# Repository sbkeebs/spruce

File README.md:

# Spruce

not the tree (actually, a split [Bruce](https://www.jlw-kb.com/products/bruce-the-keyboard-the-pcb)).

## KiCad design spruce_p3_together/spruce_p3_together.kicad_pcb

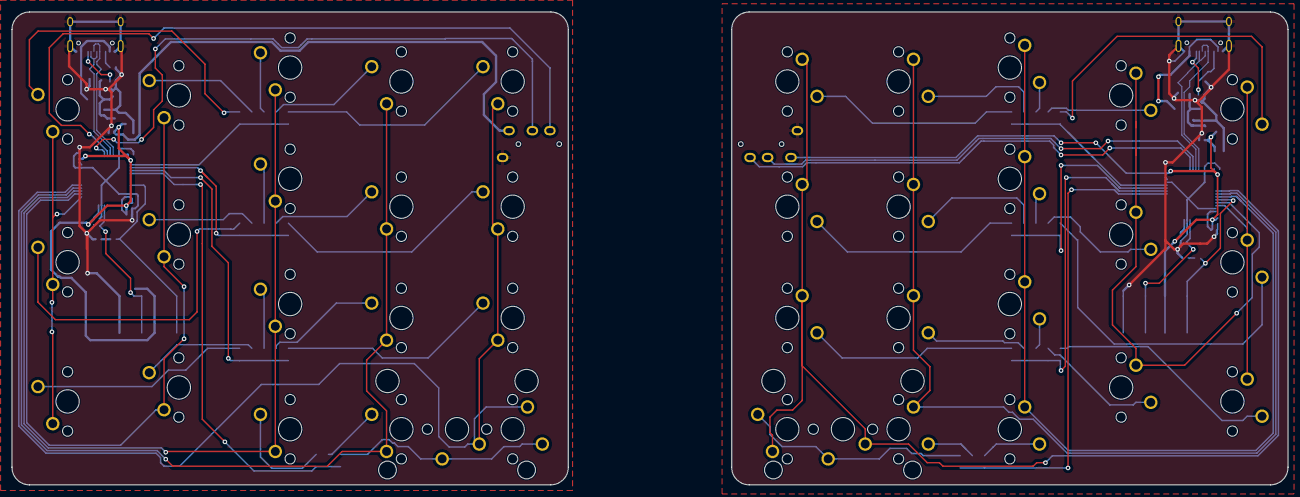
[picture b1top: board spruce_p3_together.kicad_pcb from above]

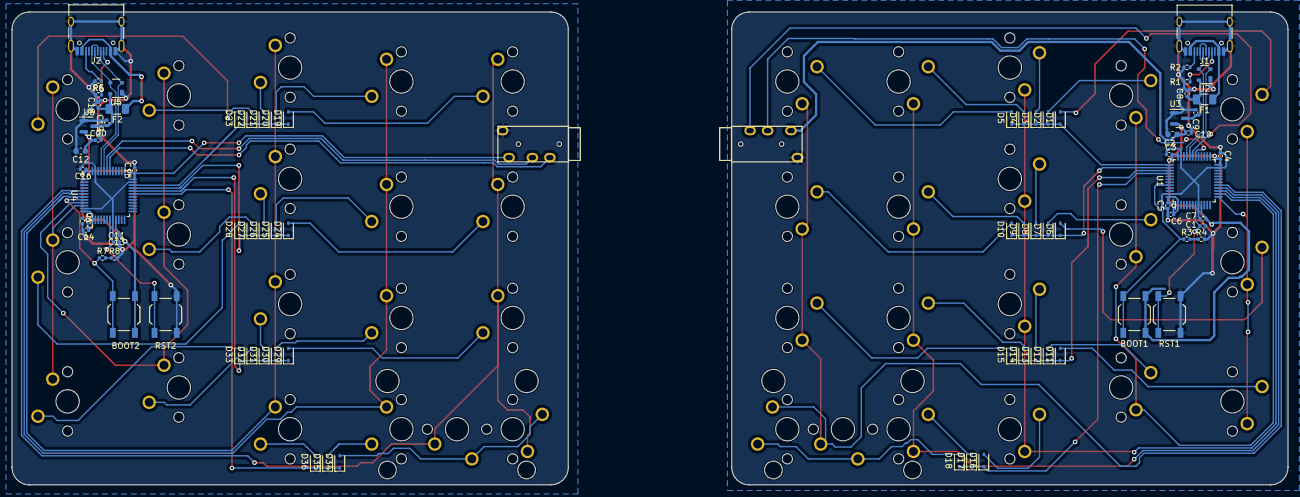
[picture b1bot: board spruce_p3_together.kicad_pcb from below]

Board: 2 copper layers, 218.5 x 81.0 mm, 120 parts (80 on the bottom side), 80 nets.

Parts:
BOOT1, BOOT2: SW_SPST; SW_SPST_TL3342
C1, C3, C4, C5, C6, C7, C8, C11, C13, C14, C15, C16, C17, C18: 100nF; C_0402_1005Metric
C2, C12: 10uF; C_0603_1608Metric
C9, C10, C19, C20: 1uF; C_0402_1005Metric
D1, D2, D3, D4, D5, D6, D7, D8, D9, D10, D11, D12, D13, D14, D15, D16, D17, D18, D19, D20, D21, D22, D23, D24, D25, D26, D27, D28, D29, D30, D31, D32, D33, D34, D35, D36: D_Small; D_SOD-323
F1, F2: 500mA; Fuse_1206_3216Metric
J1, J2: USB_C_Receptacle_USB2.0; USB_C_Receptacle_HRO_TYPE-C-31-M-12
L_MX1, L_MX12: MX_SW_solder; SW_MX_1.75u
L_MX2, L_MX11: MX_SW_solder; SW_MX_1.5u
L_MX3, L_MX6, L_MX7, L_MX8, L_MX9, L_MX10, L_MX14, L_MX15, L_MX16, L_MX17, L_MX18, L_MX19: MX_SW_solder; SW_MX_1u
L_MX4, L_MX5, L_MX13: MX_SW_solder; SW_MX_1.25u
R1, R2, R3, R4, R5, R6, R7, R8: 5.1k; R_0402_1005Metric
RST1, RST2: SW_SPST; SW_SPST_TL3342
R_MX1, R_MX2, R_MX13: MX_SW_solder; SW_MX_1.25u
R_MX3, R_MX6, R_MX7, R_MX8, R_MX9, R_MX10, R_MX11, R_MX12, R_MX16, R_MX17, R_MX18, R_MX19: MX_SW_solder; SW_MX_1u
R_MX4, R_MX15: MX_SW_solder; SW_MX_1.5u
R_MX5, R_MX14: MX_SW_solder; SW_MX_1.75u
S1, S2: MX_stab; STAB_MX_2u
U1, U4: STM32F072CBT6; LQFP-48_7x7mm_P0.5mm
U2, U5: PRTR5V0U2X; SOT-143
U3, U6: XC6206PxxxMR-Regulator_Linear; SOT-23
U7, U8: TRRS; TRRS-PJ-320A

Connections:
+3.3VA: BOOT2.1 (A), C12.1, C13.1, C14.1, C15.1, C16.1, C17.1, C20.1, U4.1 (VBAT), U4.9 (VDDA), U4.24 (VDD), U4.36 (VDDIO2), U4.48 (VDD), U6.2 (VO), U8.2 (TIP)
+3V3: BOOT1.1 (A), C2.1, C3.1, C4.1, C5.1, C6.1, C7.1, C10.1, U1.1 (VBAT), U1.9 (VDDA), U1.24 (VDD), U1.36 (VDDIO2), U1.48 (VDD), U3.2 (VO), U7.2 (TIP)
+5V: C8.1, C9.1, F1.2, U2.4 (VCC), U3.3 (VI)
+5VA: C18.1, C19.1, F2.2, U5.4 (VCC), U6.3 (VI)
GND: C1.2, C2.2, C3.2, C4.2, C5.2, C6.2, C7.2, C8.2, C9.2, C10.2, J1.A1 (GND), J1.A12 (GND), J1.B1 (GND), J1.B12 (GND), J1.S1 (SHIELD), R1.1, R2.2, R4.2, RST1.2 (B), U1.8 (VSSA), U1.23 (VSS), U1.35 (VSS), U1.47 (VSS), U2.1 (GND), U3.1 (GND), U7.1 (SLEEVE)
GND1: C11.2, C12.2, C13.2, C14.2, C15.2, C16.2, C17.2, C18.2, C19.2, C20.2, J2.A1 (GND), J2.A12 (GND), J2.B1 (GND), J2.B12 (GND), J2.S1 (SHIELD), R5.1, R6.2, R8.2, RST2.2 (B), U4.8 (VSSA), U4.23 (VSS), U4.35 (VSS), U4.47 (VSS), U5.1 (GND), U6.1 (GND), U8.1 (SLEEVE)
L_BOOT0: BOOT1.2 (B), R3.1, U1.44 (BOOT0)
L_C0: L_MX1.1, L_MX6.1, L_MX11.1, U1.13 (PA3)
L_C1: L_MX2.1, L_MX7.1, L_MX12.1, U1.14 (PA4)
L_C2: L_MX3.1, L_MX8.1, L_MX13.1, L_MX16.1, U1.15 (PA5)
L_C3: L_MX4.1, L_MX9.1, L_MX14.1, L_MX17.1, U1.16 (PA6)
L_C4: L_MX5.1, L_MX10.1, L_MX15.1, L_MX18.1, L_MX19.1, U1.17 (PA7)
L_D+: J1.A6 (D+), J1.B6 (D+), U1.33 (PA12), U2.3 (I/O2)
L_D-: J1.A7 (D-), J1.B7 (D-), U1.32 (PA11), U2.2 (I/O1)
L_NRST: C1.1, RST1.1 (A), U1.7 (NRST)
L_R0: D1.1 (K), D2.1 (K), D3.1 (K), D4.1 (K), D5.1 (K), U1.37 (PA14)
L_R1: D6.1 (K), D7.1 (K), D8.1 (K), D9.1 (K), D10.1 (K), U1.38 (PA15)
L_R2: D11.1 (K), D12.1 (K), D13.1 (K), D14.1 (K), D15.1 (K), U1.39 (PB3)
L_R3: D16.1 (K), D17.1 (K), D18.1 (K), U1.40 (PB4)
L_RX: U1.31 (PA10), U7.4 (RING2)
L_TX: U1.30 (PA9), U7.3 (RING1)
L_VBUS: F1.1, J1.A4 (VBUS), J1.A9 (VBUS), J1.B4 (VBUS), J1.B9 (VBUS)
unnamed: D1.2 (A), L_MX1.2
unnamed: D2.2 (A), L_MX2.2
unnamed: D3.2 (A), L_MX3.2
unnamed: D4.2 (A), L_MX4.2
unnamed: D5.2 (A), L_MX5.2
unnamed: D6.2 (A), L_MX6.2
unnamed: D7.2 (A), L_MX7.2
unnamed: D8.2 (A), L_MX8.2
unnamed: D9.2 (A), L_MX9.2
unnamed: D10.2 (A), L_MX10.2
unnamed: D11.2 (A), L_MX11.2
unnamed: D12.2 (A), L_MX12.2
unnamed: D13.2 (A), L_MX13.2
unnamed: D14.2 (A), L_MX14.2
unnamed: D15.2 (A), L_MX15.2
unnamed: D16.2 (A), L_MX16.2
unnamed: D17.2 (A), L_MX17.2
unnamed: D18.2 (A), L_MX18.2, L_MX19.2
unnamed: D19.2 (A), R_MX1.2
unnamed: D20.2 (A), R_MX2.2
unnamed: D21.2 (A), R_MX3.2
unnamed: D22.2 (A), R_MX4.2
unnamed: D23.2 (A), R_MX5.2
unnamed: D24.2 (A), R_MX6.2
unnamed: D25.2 (A), R_MX7.2
unnamed: D26.2 (A), R_MX8.2
unnamed: D27.2 (A), R_MX9.2
unnamed: D28.2 (A), R_MX10.2
unnamed: D29.2 (A), R_MX11.2
unnamed: D30.2 (A), R_MX12.2
unnamed: D31.2 (A), R_MX13.2
unnamed: D32.2 (A), R_MX14.2
unnamed: D33.2 (A), R_MX15.2
unnamed: D34.2 (A), R_MX16.2, R_MX17.2
unnamed: D35.2 (A), R_MX18.2
unnamed: D36.2 (A), R_MX19.2
unnamed: J1.A5 (CC1), R1.2
unnamed: J1.B5 (CC2), R2.1
unnamed: J2.A5 (CC1), R5.2
unnamed: J2.B5 (CC2), R6.1
unnamed: R3.2, R4.1
unnamed: R7.2, R8.1
R_BOOT0: BOOT2.2 (B), R7.1, U4.44 (BOOT0)
R_C0: R_MX1.1, R_MX6.1, R_MX11.1, R_MX16.1, R_MX17.1, U4.41 (PB5)
R_C1: R_MX2.1, R_MX7.1, R_MX12.1, R_MX18.1, U4.42 (PB6)
R_C2: R_MX3.1, R_MX8.1, R_MX13.1, R_MX19.1, U4.43 (PB7)
R_C3: R_MX4.1, R_MX9.1, R_MX14.1, U4.45 (PB8)
R_C4: R_MX5.1, R_MX10.1, R_MX15.1, U4.46 (PB9)
R_D+: J2.A6 (D+), J2.B6 (D+), U4.33 (PA12), U5.3 (I/O2)
R_D-: J2.A7 (D-), J2.B7 (D-), U4.32 (PA11), U5.2 (I/O1)
R_NRST: C11.1, RST2.1 (A), U4.7 (NRST)
R_R0: D19.1 (K), D20.1 (K), D21.1 (K), D22.1 (K), D23.1 (K), U4.22 (PB11)
R_R1: D24.1 (K), D25.1 (K), D26.1 (K), D27.1 (K), D28.1 (K), U4.21 (PB10)
R_R2: D29.1 (K), D30.1 (K), D31.1 (K), D32.1 (K), D33.1 (K), U4.20 (PB2)
R_R3: D34.1 (K), D35.1 (K), D36.1 (K), U4.19 (PB1)
R_RX: U4.31 (PA10), U8.3 (RING1)
R_TX: U4.30 (PA9), U8.4 (RING2)
R_VBUS: F2.1, J2.A4 (VBUS), J2.A9 (VBUS), J2.B4 (VBUS), J2.B9 (VBUS)

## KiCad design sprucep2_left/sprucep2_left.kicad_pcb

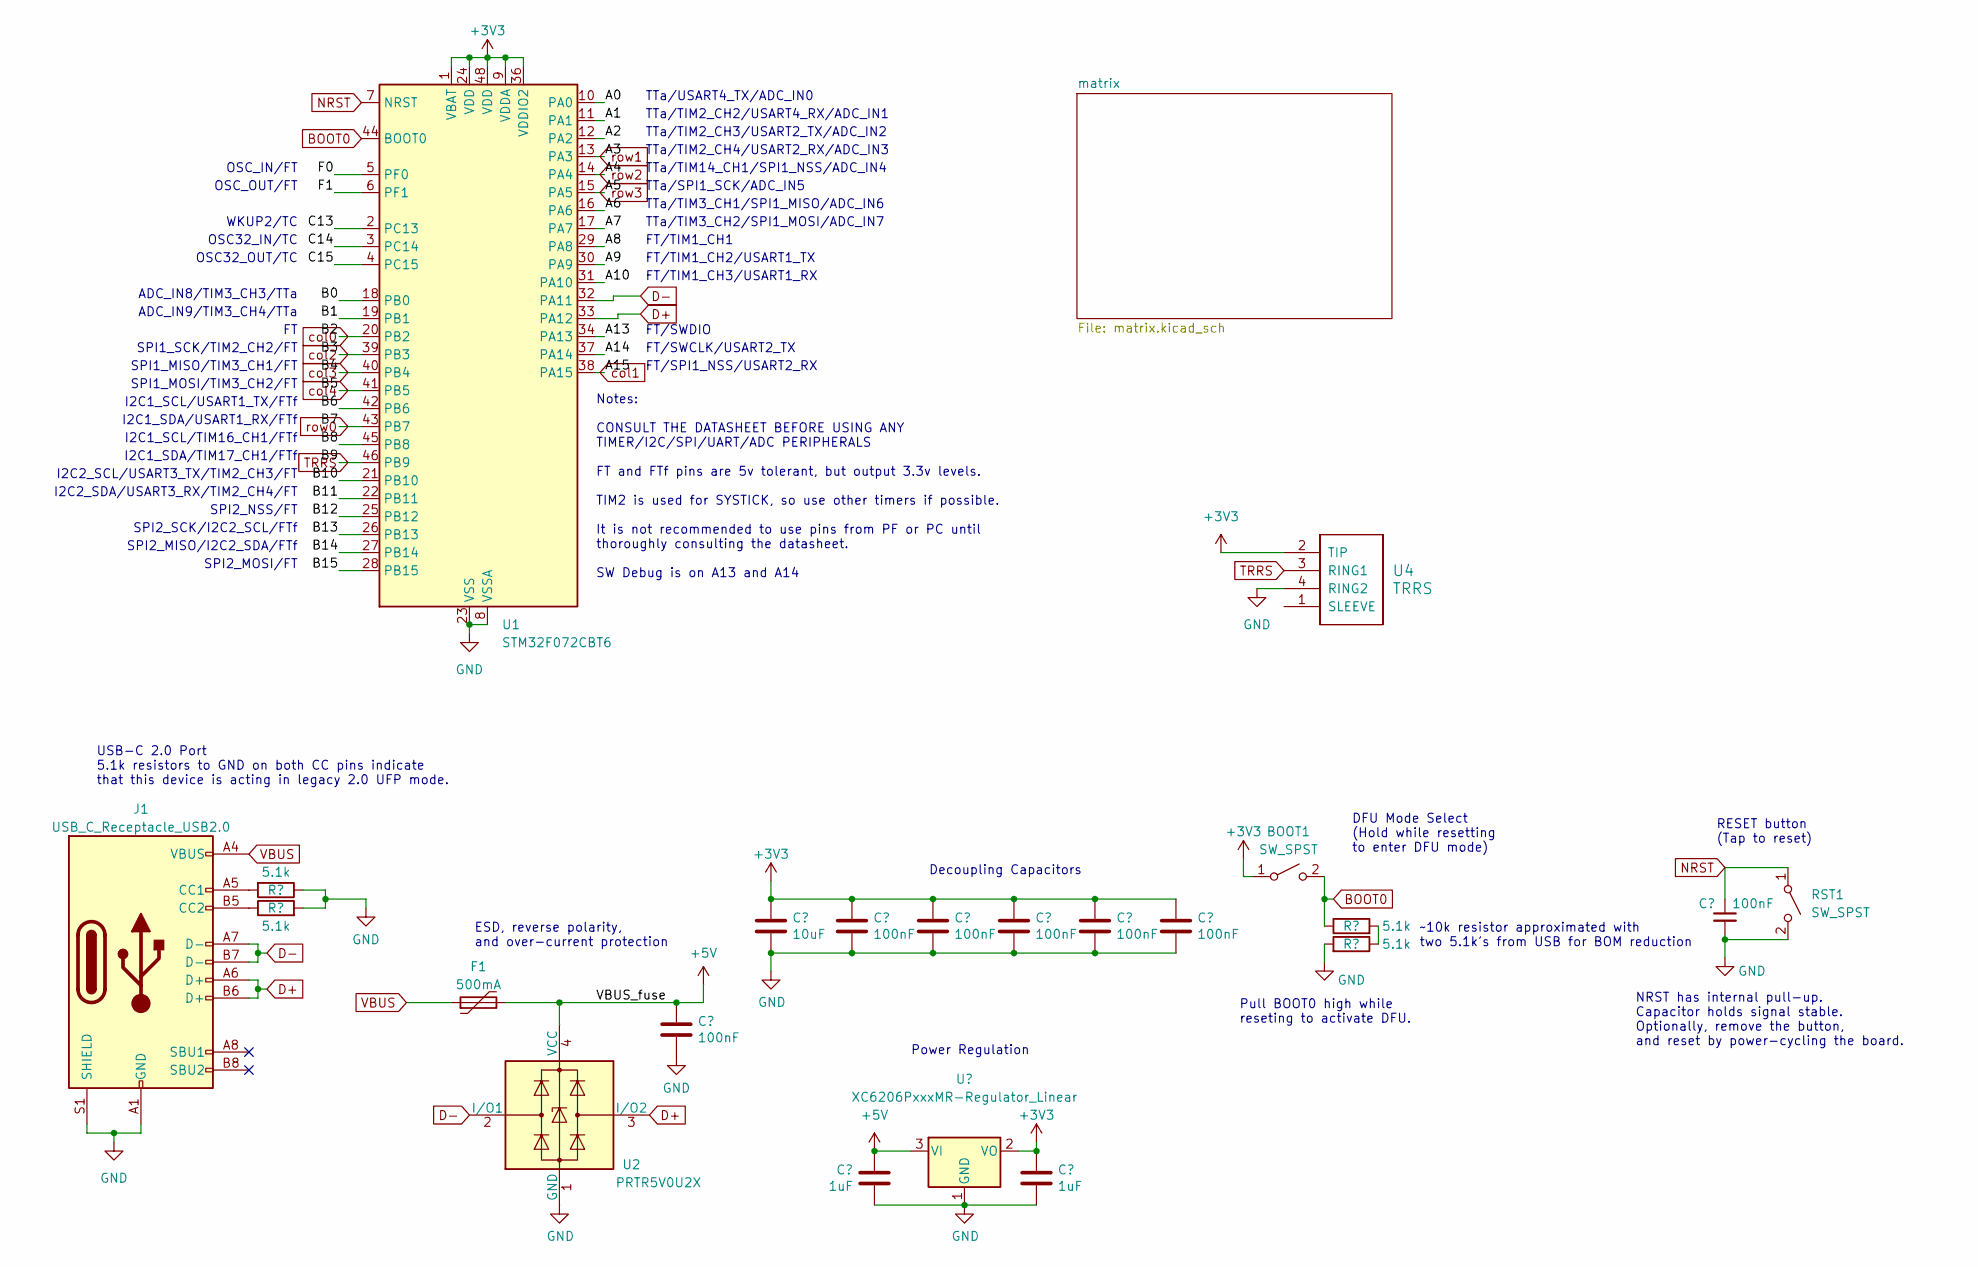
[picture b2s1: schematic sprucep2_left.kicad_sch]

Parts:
BOOT1: SW_SPST; SW_SPST_TL3342
C1, C3, C4, C5, C6, C7, C8: 100nF; C_0402_1005Metric; LCSC C307331
C2: 10uF; C_0603_1608Metric; LCSC C307331
C9, C10: 1uF; C_0402_1005Metric; LCSC C307331
F1: 500mA; Fuse_1206_3216Metric; LCSC C135341
J1: USB_C_Receptacle_USB2.0; USB_C_Receptacle_HRO_TYPE-C-31-M-12; JlcRotOffset 180
R1, R2, R3, R4: 5.1k; R_0402_1005Metric
RST1: SW_SPST; SW_SPST_TL3342
U1: STM32F072CBT6; LQFP-48_7x7mm_P0.5mm; JlcRotOffset 90
U2: PRTR5V0U2X; SOT-143; LCSC C2827688
U3: XC6206PxxxMR-Regulator_Linear; SOT-23; LCSC C5446
U4: TRRS; TRRS-PJ-320A

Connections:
+3V3: C2.1, C3.1, C4.1, C5.1, C6.1, C7.1, C10.1, U1.1 (VBAT), U1.9 (VDDA), U1.24 (VDD), U1.36 (VDDIO2), U1.48 (VDD), U3.2 (VO), U4.2 (TIP); also elsewhere on the board
+5V: C8.1, C9.1, F1.2, U2.4 (VCC), U3.3 (VI)
/A0: U1.10 (PA0)
/A1: U1.11 (PA1)
/A2: U1.12 (PA2)
/A6: U1.16 (PA6)
/A7: U1.17 (PA7)
/A8: U1.29 (PA8)
/A9: U1.30 (PA9)
/A10: U1.31 (PA10)
/A13: U1.34 (PA13)
/A14: U1.37 (PA14)
/B0: U1.18 (PB0)
/B1: U1.19 (PB1)
/B6: U1.42 (PB6)
/B8: U1.45 (PB8)
/B10: U1.21 (PB10)
/B11: U1.22 (PB11)
/B12: U1.25 (PB12)
/B13: U1.26 (PB13)
/B14: U1.27 (PB14)
/B15: U1.28 (PB15)
/C13: U1.2 (PC13)
/C14: U1.3 (PC14)
/C15: U1.4 (PC15)
/F0: U1.5 (PF0)
/F1: U1.6 (PF1)
BOOT0: R3.1, U1.44 (BOOT0); also elsewhere on the board
D+: J1.A6 (D+), J1.B6 (D+), U1.33 (PA12), U2.3 (I/O2)
D-: J1.A7 (D-), J1.B7 (D-), U1.32 (PA11), U2.2 (I/O1)
GND: C1.2, C2.2, C3.2, C4.2, C5.2, C6.2, C7.2, C8.2, C9.2, C10.2, J1.A1 (GND), J1.A12 (GND), J1.B1 (GND), J1.B12 (GND), J1.S1 (SHIELD), R1.1, R2.2, R4.2, U1.8 (VSSA), U1.23 (VSS), U1.35 (VSS), U1.47 (VSS), U2.1 (GND), U3.1 (GND), U4.4 (RING2); also elsewhere on the board
NRST: C1.1, U1.7 (NRST); also elsewhere on the board
unnamed: J1.A5 (CC1), R1.2
unnamed: J1.B5 (CC2), R2.1
unnamed: R3.2, R4.1
TRRS: U1.46 (PB9), U4.3 (RING1)
VBUS: F1.1, J1.A4 (VBUS), J1.A9 (VBUS), J1.B4 (VBUS), J1.B9 (VBUS)
col0: U1.20 (PB2); also elsewhere on the board
col1: U1.38 (PA15); also elsewhere on the board
col2: U1.39 (PB3); also elsewhere on the board
col3: U1.40 (PB4); also elsewhere on the board
col4: U1.41 (PB5); also elsewhere on the board
row0: U1.43 (PB7); also elsewhere on the board
row1: U1.13 (PA3); also elsewhere on the board
row2: U1.14 (PA4); also elsewhere on the board
row3: U1.15 (PA5); also elsewhere on the board

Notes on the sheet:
SPI1_SCK/TIM2_CH2/FT
FT/TIM1_CH1
FT/TIM1_CH3/USART1_RX
SPI2_NSS/FT
Notes: CONSULT THE DATASHEET BEFORE USING ANY TIMER/I2C/SPI/UART/ADC PERIPHERALS FT and FTf pins are 5v tolerant, but output 3.3v levels. TIM2 is used for SYSTICK, so use other timers if possible. It is not recommended to use pins from PF or PC until thoroughly consulting the datasheet. SW Debug is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
TTa/TIM2_CH4/USART2_RX/ADC_IN3
NRST has internal pull-up. Capacitor holds signal stable. Optionally, remove the button, and reset by power-cycling the board.
FT/SWDIO
Decoupling Capacitors
SPI1_MOSI/TIM3_CH2/FT
ADC_IN9/TIM3_CH4/TTa
I2C2_SCL/USART3_TX/TIM2_CH3/FT
SPI2_MISO/I2C2_SDA/FTf
FT/SWCLK/USART2_TX
I2C1_SCL/TIM16_CH1/FTf
~10k resistor approximated with two 5.1k's from USB for BOM reduction
TTa/TIM2_CH2/USART4_RX/ADC_IN1
USB-C 2.0 Port 5.1k resistors to GND on both CC pins indicate that this device is acting in legacy 2.0 UFP mode.
TTa/TIM2_CH3/USART2_TX/ADC_IN2
OSC_IN/FT
DFU Mode Select (Hold while resetting to enter DFU mode)
WKUP2/TC
I2C2_SDA/USART3_RX/TIM2_CH4/FT
ADC_IN8/TIM3_CH3/TTa
RESET button (Tap to reset)
Pull BOOT0 high while reseting to activate DFU.
I2C1_SDA/TIM17_CH1/FTf
TTa/SPI1_SCK/ADC_IN5
TTa/TIM3_CH1/SPI1_MISO/ADC_IN6
TTa/TIM3_CH2/SPI1_MOSI/ADC_IN7
OSC32_OUT/TC
FT/SPI1_NSS/USART2_RX
SPI1_MISO/TIM3_CH1/FT
OSC32_IN/TC
TTa/TIM14_CH1/SPI1_NSS/ADC_IN4
I2C1_SDA/USART1_RX/FTf
SPI2_MOSI/FT
FT/TIM1_CH2/USART1_TX
Power Regulation
SPI2_SCK/I2C2_SCL/FTf

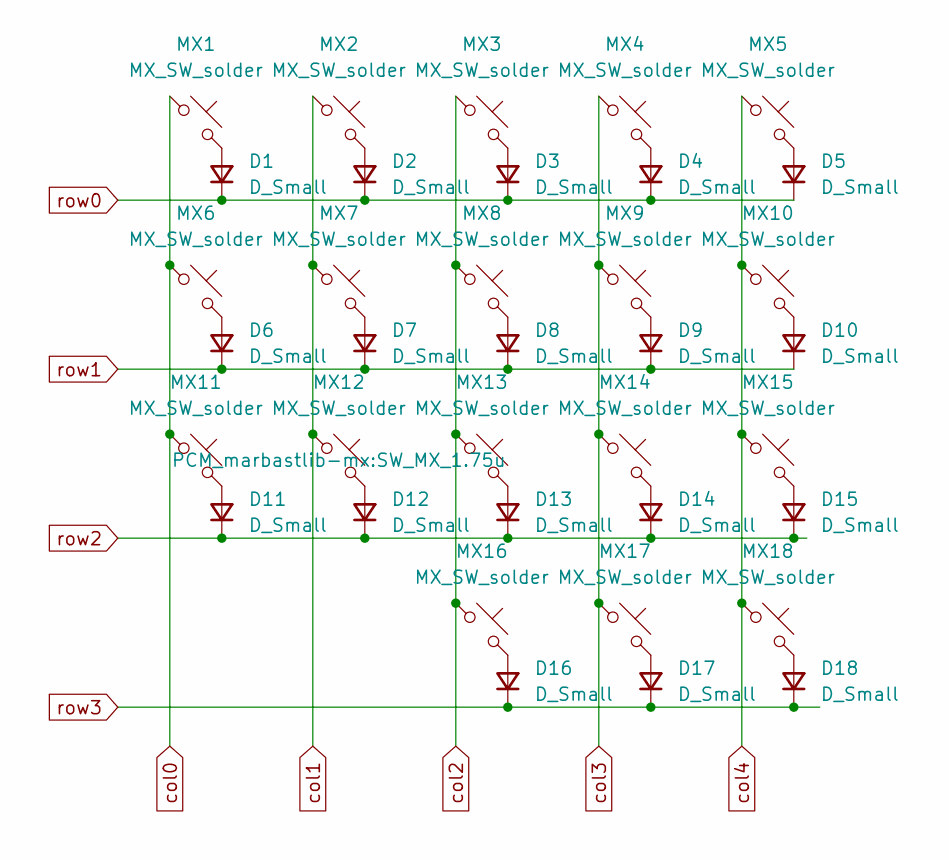
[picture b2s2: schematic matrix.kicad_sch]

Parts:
D1, D2, D3, D4, D5, D6, D7, D8, D9, D10, D11, D12, D13, D14, D15, D16, D17, D18: D_Small; D_SOD-323
MX1, MX12: MX_SW_solder; SW_MX_1.75u
MX2, MX11: MX_SW_solder; SW_MX_1.5u
MX3, MX6, MX7, MX8, MX9, MX10, MX14, MX15, MX16, MX17, MX18: MX_SW_solder; SW_MX_1u
MX4, MX5, MX13: MX_SW_solder; SW_MX_1.25u

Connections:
unnamed: D1.2 (A), MX1.2
unnamed: D2.2 (A), MX2.2
unnamed: D3.2 (A), MX3.2
unnamed: D4.2 (A), MX4.2
unnamed: D5.2 (A), MX5.2
unnamed: D6.2 (A), MX6.2
unnamed: D7.2 (A), MX7.2
unnamed: D8.2 (A), MX8.2
unnamed: D9.2 (A), MX9.2
unnamed: D10.2 (A), MX10.2
unnamed: D11.2 (A), MX11.2
unnamed: D12.2 (A), MX12.2
unnamed: D13.2 (A), MX13.2
unnamed: D14.2 (A), MX14.2
unnamed: D15.2 (A), MX15.2
unnamed: D16.2 (A), MX16.2
unnamed: D17.2 (A), MX17.2
unnamed 49: D18.2 (A), MX18.2; also elsewhere on the board
col0: MX1.1, MX6.1, MX11.1; also elsewhere on the board
col1: MX2.1, MX7.1, MX12.1; also elsewhere on the board
col2: MX3.1, MX8.1, MX13.1, MX16.1; also elsewhere on the board
col3: MX4.1, MX9.1, MX14.1, MX17.1; also elsewhere on the board
col4: MX5.1, MX10.1, MX15.1, MX18.1; also elsewhere on the board
row0: D1.1 (K), D2.1 (K), D3.1 (K), D4.1 (K), D5.1 (K); also elsewhere on the board
row1: D6.1 (K), D7.1 (K), D8.1 (K), D9.1 (K), D10.1 (K); also elsewhere on the board
row2: D11.1 (K), D12.1 (K), D13.1 (K), D14.1 (K), D15.1 (K); also elsewhere on the board
row3: D16.1 (K), D17.1 (K), D18.1 (K); also elsewhere on the board

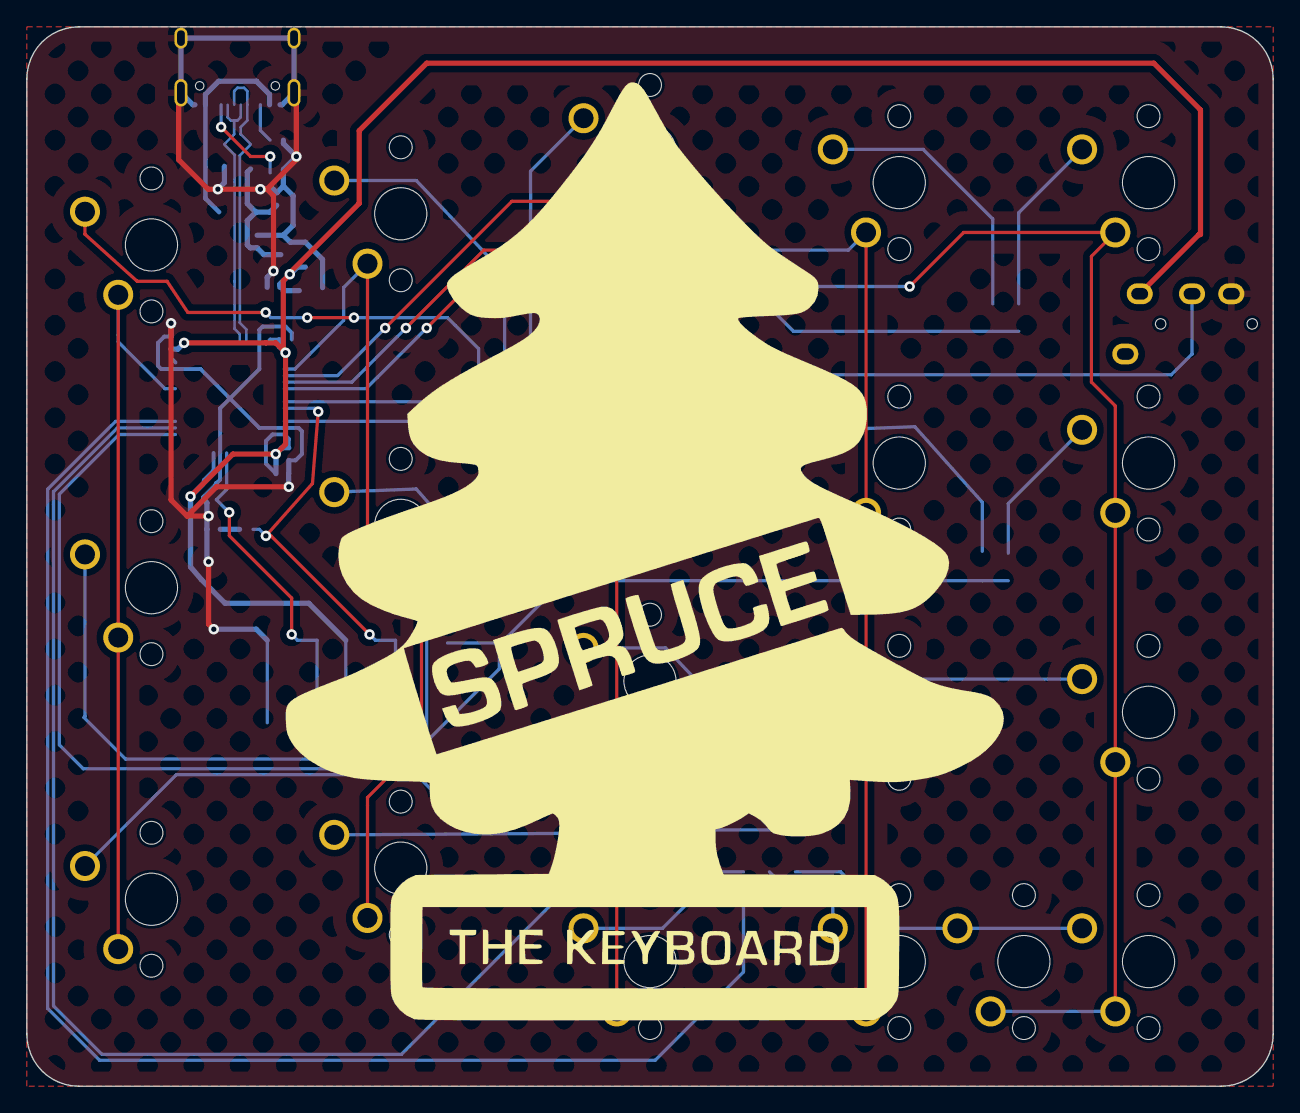
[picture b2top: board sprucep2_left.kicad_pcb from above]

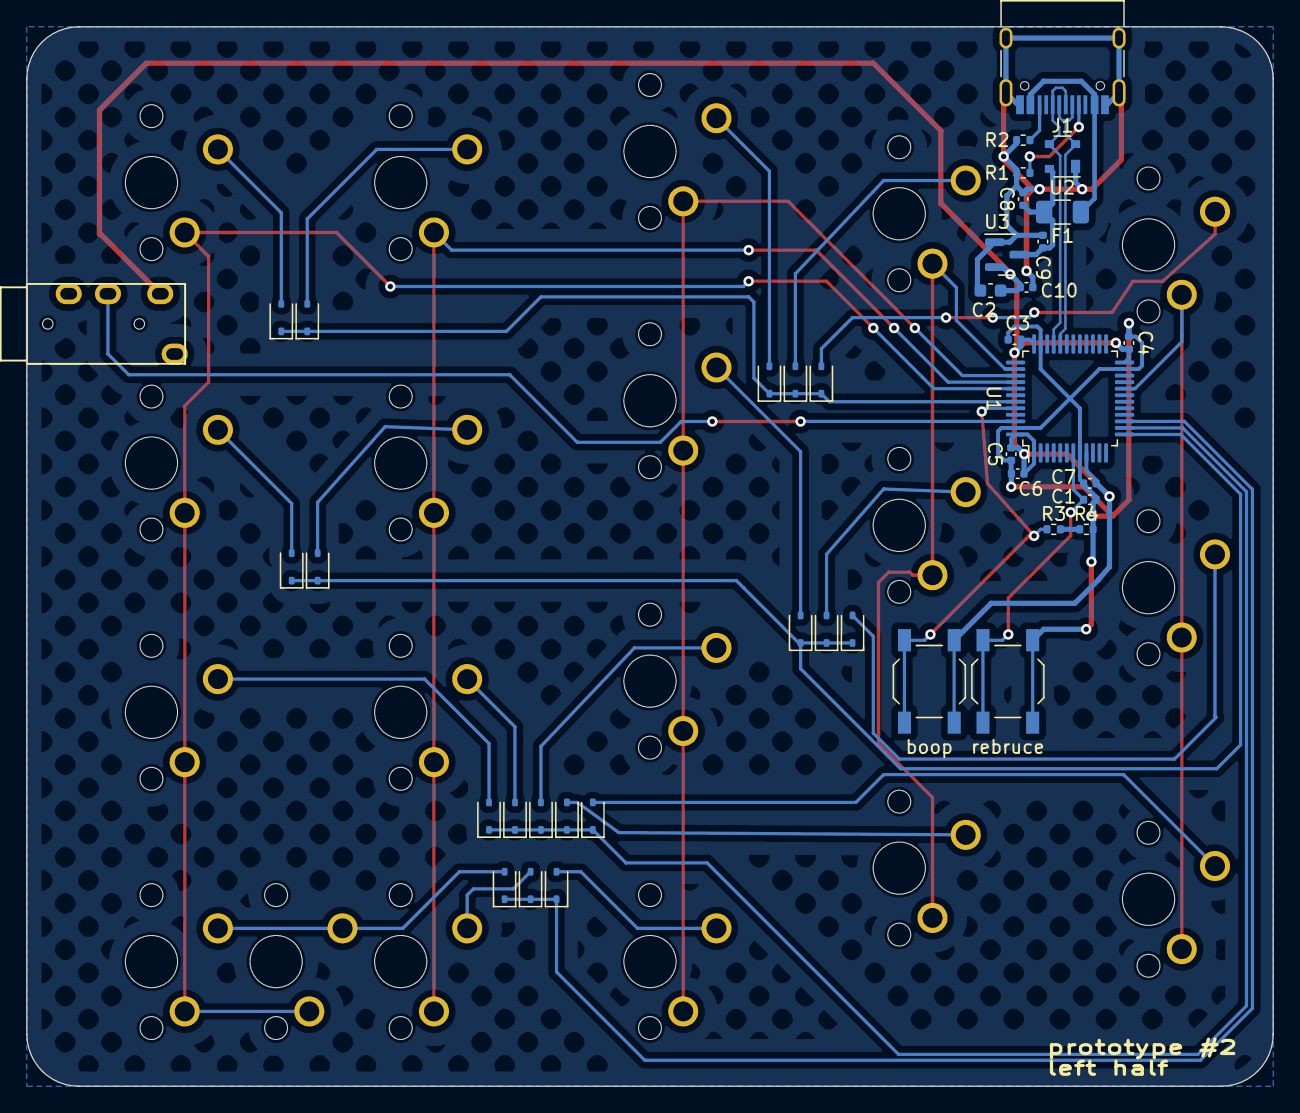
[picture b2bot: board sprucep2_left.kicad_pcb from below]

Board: 2 copper layers, 95.2 x 81.0 mm, 59 parts (40 on the bottom side), 39 nets.

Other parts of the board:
MX18#2: MX_SW_solder; SW_MX_1u
boop: SW_SPST; SW_SPST_TL3342
rebruce: SW_SPST; SW_SPST_TL3342

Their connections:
+3V3: boop.1 (A); also elsewhere on the board
BOOT0: boop.2 (B); also elsewhere on the board
GND: rebruce.2 (B); also elsewhere on the board
NRST: rebruce.1 (A); also elsewhere on the board
unnamed 49: MX18#2.2; also elsewhere on the board
col4: MX18#2.1; also elsewhere on the board

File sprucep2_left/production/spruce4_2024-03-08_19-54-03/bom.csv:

Designator,Footprint,Quantity,Value,LCSC Part #
"C1, C3, C4, C5, C6, C7, C8",0402,7,100nF,C1525
"C10, C9",0402,2,1uF,C52923
C2,0603,1,10uF,C57112
"D1, D10, D11, D12, D13, D14, D15, D16, D17, D18, D2, D3, D4, D5, D6, D7, D8, D9",D_SOD-323_no_silk,18,D_Small,C908234
F1,1206,1,500mA,C70076
J1,USB_C_Receptacle_HRO_TYPE-C-31-M-12,1,USB_C_Receptacle_USB2.0,C165948
"R1, R2, R3, R4",0402,4,5.1k,C25905
U1,LQFP-48_7x7mm_P0.5mm,1,STM32F072CBT6,C81720
U2,SOT-143,1,PRTR5V0U2X,C2827688
U3,SOT-23,1,XC6206PxxxMR-Regulator_Linear,C5446
"boop, rebruce",SW_SPST_TL3342,2,SW_SPST,C318884

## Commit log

2024-03-09 commit p2
2024-03-09 add images and readme
2024-03-09 ordering
2024-03-09 remove temp files
2024-03-09 cleanup
2024-03-09 svgs
2024-03-09 cleanup backups
2024-03-09 add sprucifer
2024-04-25 new version
2024-04-25 cleanup2
2024-04-26 routing for keys
2025-03-13 add step export with modeled trrs and usb
2025-03-13 add step export of revised bumpon plate
